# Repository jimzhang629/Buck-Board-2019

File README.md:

# Buck-Board-2019

REV buck converter board in 2019.

Converts 48V supply to 12V6A output and 12V1.6A output.

12V6A output is isolated and can be remotely turned on and off. We will use this to control our wipers and horn.

12V1.6A output will be sent to our MCU.

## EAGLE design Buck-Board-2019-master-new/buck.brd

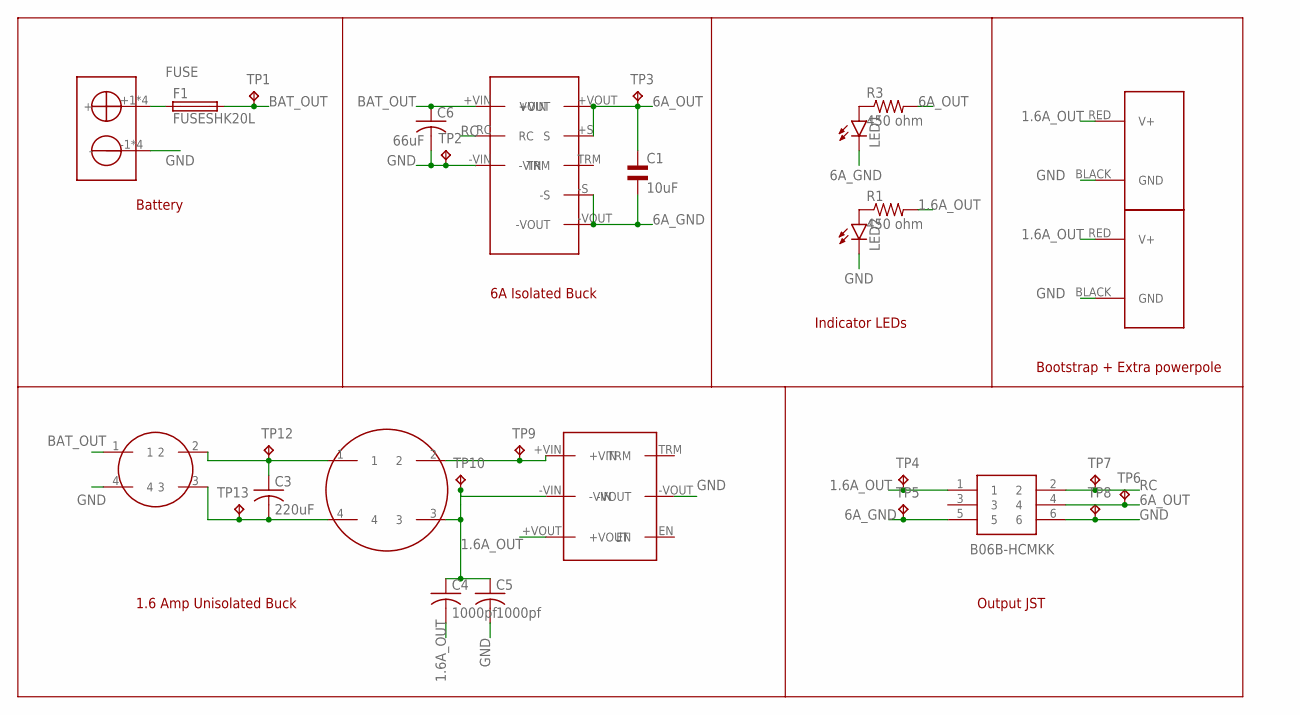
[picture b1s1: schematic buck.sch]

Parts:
BUCK150UH: CMNMODECHOKE150UH
C1: 10uF; EU25-10
C3: 220uF; C0805
C4, C5: 1000pf; C0805
C6: 66uF; C0805
CHOKEME: CMNMODECHOKE1.2MH
F1: FUSESHK20L; SHK20L
J1: B06B-HCMKK; B06BHCMKK
J2, J3: POWERPOLE_POWER45A_DRILL; POWERPOLE_PAIR_45A_HOLE
LED1, LED2: LEDCHIP-LED0603; CHIP-LED0603
R1, R3: 450 ohm; R0805
TP1, TP2, TP3, TP4, TP5, TP6, TP7, TP8, TP9, TP10, TP12, TP13: TPPAD1-13; P1-13
U$1: 12V6ABUCKCONVERTER
U$2: SB50; MINI-SB-50
U$3: BUCK1.6A

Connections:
1.6A_OUT: C4.2, J1.1, J2.RED (V+), J3.RED (V+), R1.2, TP4.TP, U$3.+VOUT
6A_GND: C1.2, J1.5, LED1.C, TP5.TP, U$1.-S, U$1.-VOUT
6A_OUT: C1.1, J1.4, R3.2, TP3.TP, TP6.TP, U$1.+S (S), U$1.+VOUT (VOUT)
BAT_OUT: BUCK150UH.1, C6.1, F1.2A (2), TP1.TP, U$1.+VIN
FUSE: F1.1A (1), U$2.+1 (+), U$2.+2 (+), U$2.+3 (+), U$2.+4 (+)
GND: BUCK150UH.4, C5.2, C6.2, J1.6, J2.BLACK (GND), J3.BLACK (GND), LED2.C, TP2.TP, TP8.TP, U$1.-VIN, U$2.-1 (-), U$2.-2 (-), U$2.-3 (-), U$2.-4 (-), U$3.-VOUT
unnamed: BUCK150UH.2, C3.1, CHOKEME.1, TP12.TP
unnamed: BUCK150UH.3, C3.2, CHOKEME.4, TP13.TP
unnamed: CHOKEME.2, TP9.TP, U$3.+VIN
unnamed: C4.1, C5.1, CHOKEME.3, TP10.TP, U$3.-VIN
unnamed: LED2.A, R1.1
unnamed: LED1.A, R3.1
RC: J1.2, TP7.TP, U$1.RC

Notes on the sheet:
1.6 Amp Unisolated Buck
6A Isolated Buck
Battery
Indicator LEDs
Output JST
Bootstrap + Extra powerpole

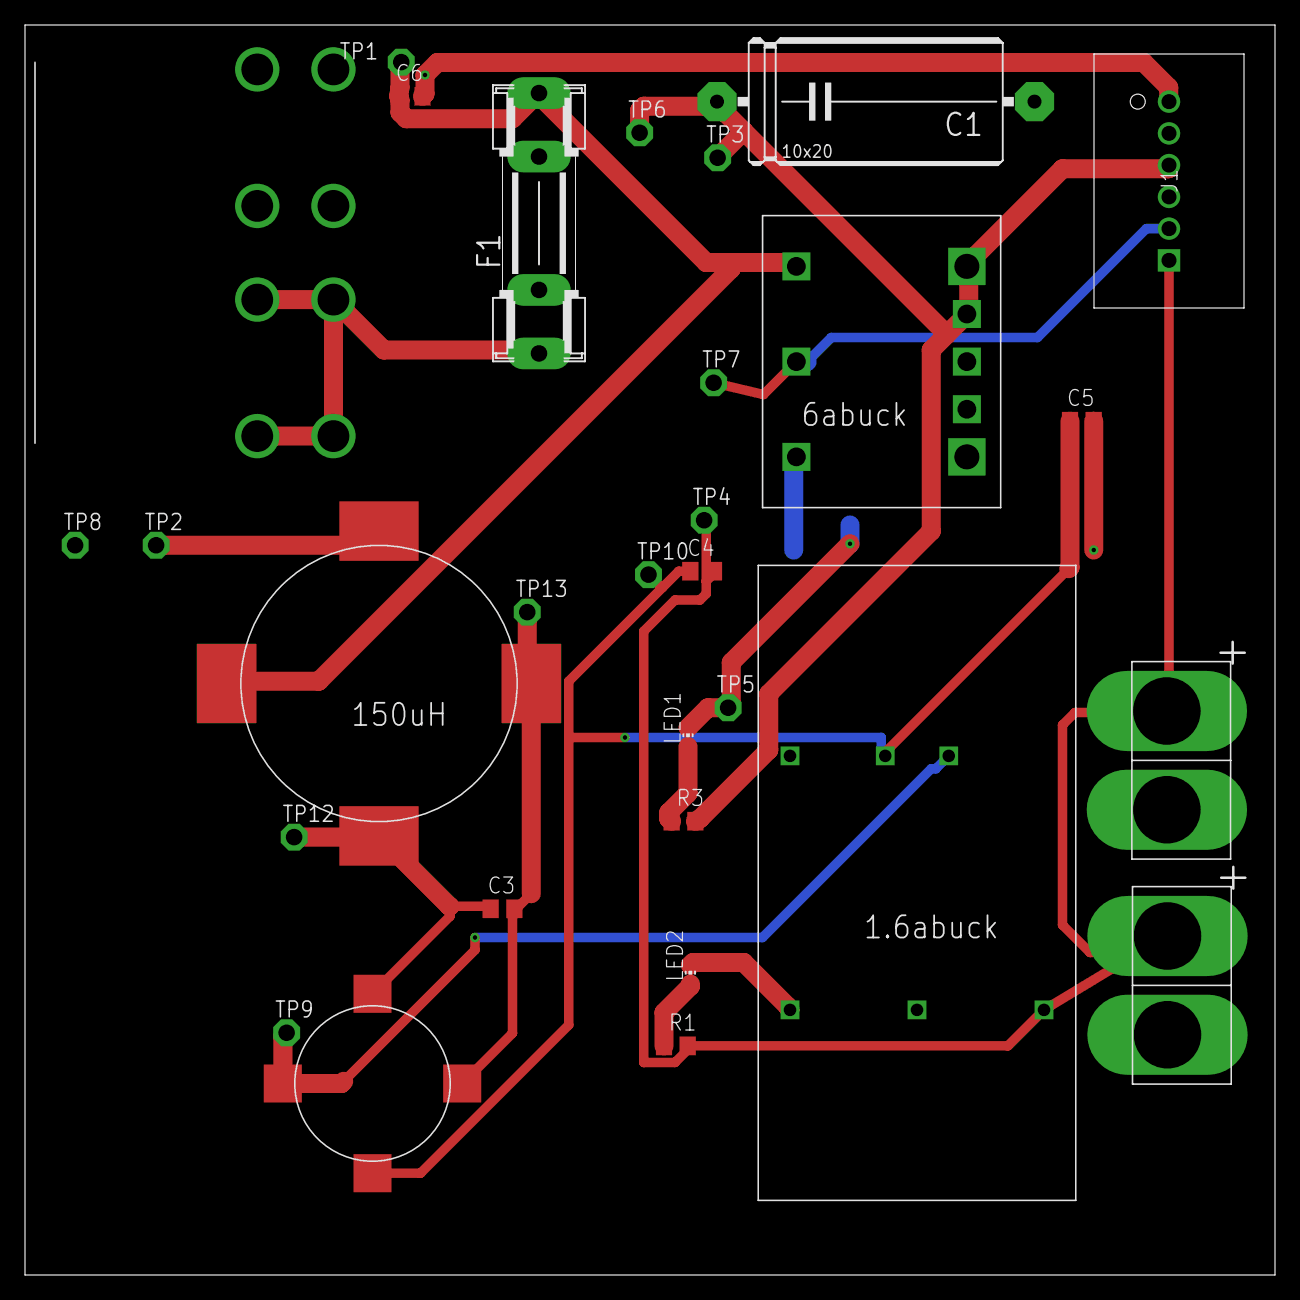
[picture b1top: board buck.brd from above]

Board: 2 copper layers, 100.0 x 100.0 mm, 30 parts (0 on the bottom side), 13 nets.

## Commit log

2019-10-26 Add files via upload
    Library for 1.6 Amp MEANWELL buckconverter
2019-10-26 Add files via upload
    Schematic for Jim's 12V6A output buck converter. Has HCM output connector.
2019-11-04 Update the schematic with new buckboard
2019-11-04 Create FolderTest
2019-11-04 Full eagle project
2019-11-04 Added REV library
2019-11-04 Add files via upload
    Autorouted shitty board. MVP.
2019-11-11 Add files via upload
    Made new board and minor clean up of schematic. Still needs the LED fixed.
2019-11-23 Add files via upload
    Updated circuit schematic
2019-11-23 Add files via upload
    yug
2019-11-25 Add files via upload
    Fattened some of the traces
2021-03-18 This code gives all false negatives.
